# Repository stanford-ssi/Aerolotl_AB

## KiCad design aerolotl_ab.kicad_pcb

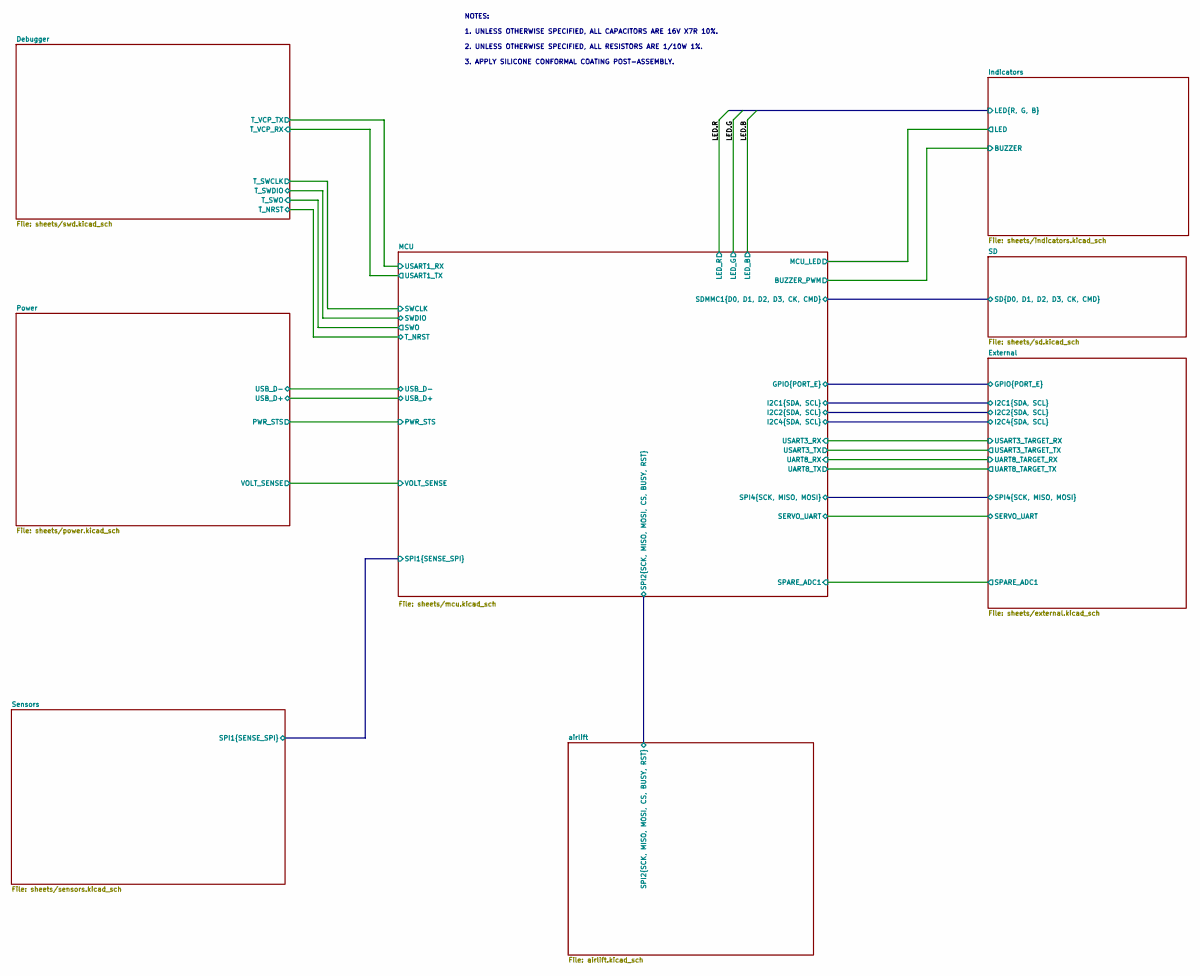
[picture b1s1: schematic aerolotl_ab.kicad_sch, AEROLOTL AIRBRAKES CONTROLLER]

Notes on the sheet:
NOTES: 1. UNLESS OTHERWISE SPECIFIED, ALL CAPACITORS ARE 16V X7R 10%. 2. UNLESS OTHERWISE SPECIFIED, ALL RESISTORS ARE 1/10W 1%. 3. APPLY SILICONE CONFORMAL COATING POST-ASSEMBLY.

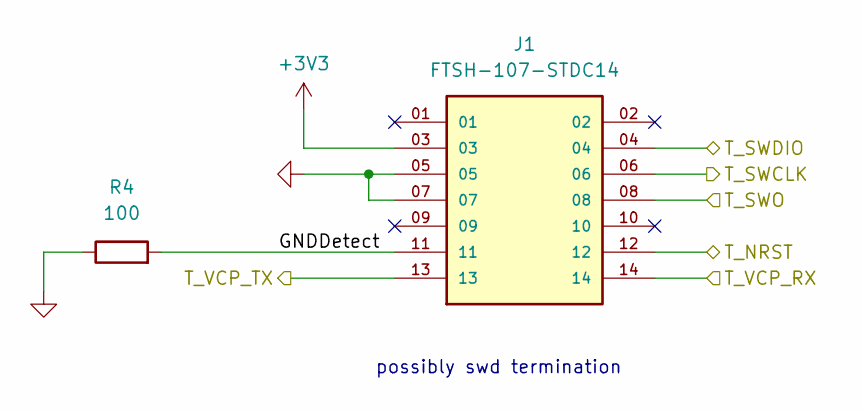
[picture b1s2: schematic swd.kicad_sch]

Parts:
J1: FTSH-107-STDC14; STDC14_SAMTEC_FTSH-107-01-L-DV-K-A; PARTREV H
R4: 100; R_0402_1005Metric

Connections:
+3V3: J1.03; also elsewhere on the board
/Debugger/GNDDetect: J1.11, R4.2
/Debugger/T_NRST: J1.12; also elsewhere on the board
/Debugger/T_SWCLK: J1.06; also elsewhere on the board
/Debugger/T_SWDIO: J1.04; also elsewhere on the board
/Debugger/T_SWO: J1.08; also elsewhere on the board
/Debugger/T_VCP_RX: J1.14; also elsewhere on the board
/Debugger/T_VCP_TX: J1.13; also elsewhere on the board
GND: J1.05, J1.07, R4.1; also elsewhere on the board

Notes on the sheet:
possibly swd termination

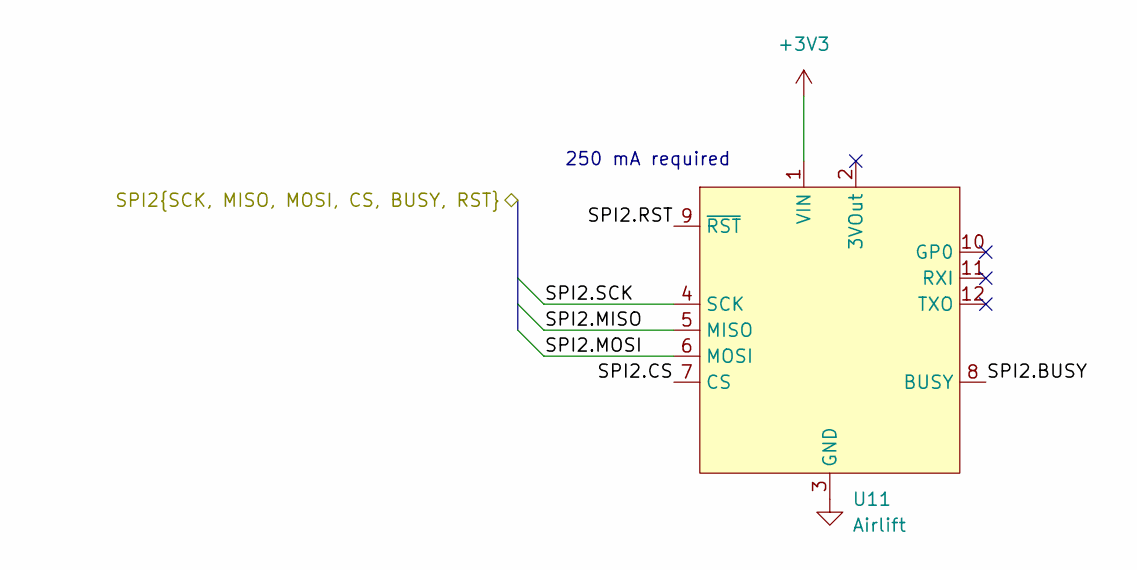
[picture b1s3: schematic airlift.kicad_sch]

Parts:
U11: Airlift; PinSocket_1x12_P2.54mm_Vertical; Mfr. Part No. 4201

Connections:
+3V3: U11.1 (VIN); also elsewhere on the board
/MCU/SPI2.BUSY: U11.8 (BUSY); also elsewhere on the board
/MCU/SPI2.CS: U11.7 (CS); also elsewhere on the board
/MCU/SPI2.MISO: U11.5 (MISO); also elsewhere on the board
/MCU/SPI2.MOSI: U11.6 (MOSI); also elsewhere on the board
/MCU/SPI2.RST: U11.9 (~RST); also elsewhere on the board
/MCU/SPI2.SCK: U11.4 (SCK); also elsewhere on the board
GND: U11.3 (GND); also elsewhere on the board

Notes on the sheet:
250 mA required

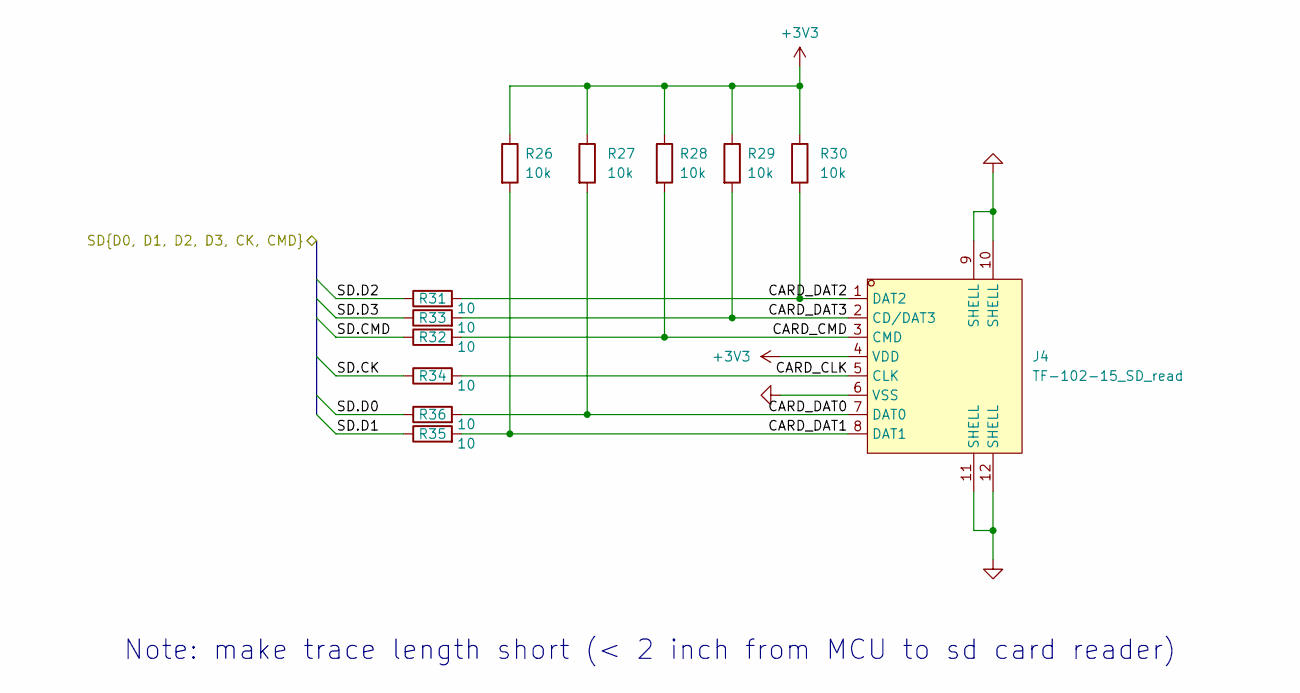
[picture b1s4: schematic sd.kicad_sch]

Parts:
J4: TF-102-15_SD_read; TF-SMD_TF-102-15; LCSC Part C266609
R26, R27, R28, R29, R30: 10k; R_0402_1005Metric; LCSC Part C25744
R31, R32, R33, R34, R35, R36: 10; R_0402_1005Metric

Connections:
+3V3: J4.4 (VDD), R26.1, R27.1, R28.1, R29.1, R30.1; also elsewhere on the board
/MCU/SDMMC1.CK: R34.1; also elsewhere on the board
/MCU/SDMMC1.CMD: R32.1; also elsewhere on the board
/MCU/SDMMC1.D0: R36.1; also elsewhere on the board
/MCU/SDMMC1.D1: R35.1; also elsewhere on the board
/MCU/SDMMC1.D2: R31.1; also elsewhere on the board
/MCU/SDMMC1.D3: R33.1; also elsewhere on the board
/SD/CARD_CLK: J4.5 (CLK), R34.2
/SD/CARD_CMD: J4.3 (CMD), R28.2, R32.2
/SD/CARD_DAT0: J4.7 (DAT0), R27.2, R36.2
/SD/CARD_DAT1: J4.8 (DAT1), R26.2, R35.2
/SD/CARD_DAT2: J4.1 (DAT2), R30.2, R31.2
/SD/CARD_DAT3: J4.2 (CD/DAT3), R29.2, R33.2
GND: J4.6 (VSS), J4.9 (SHELL), J4.10 (SHELL), J4.11 (SHELL), J4.12 (SHELL); also elsewhere on the board

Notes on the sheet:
Note: make trace length short (< 2 inch from MCU to sd card reader)

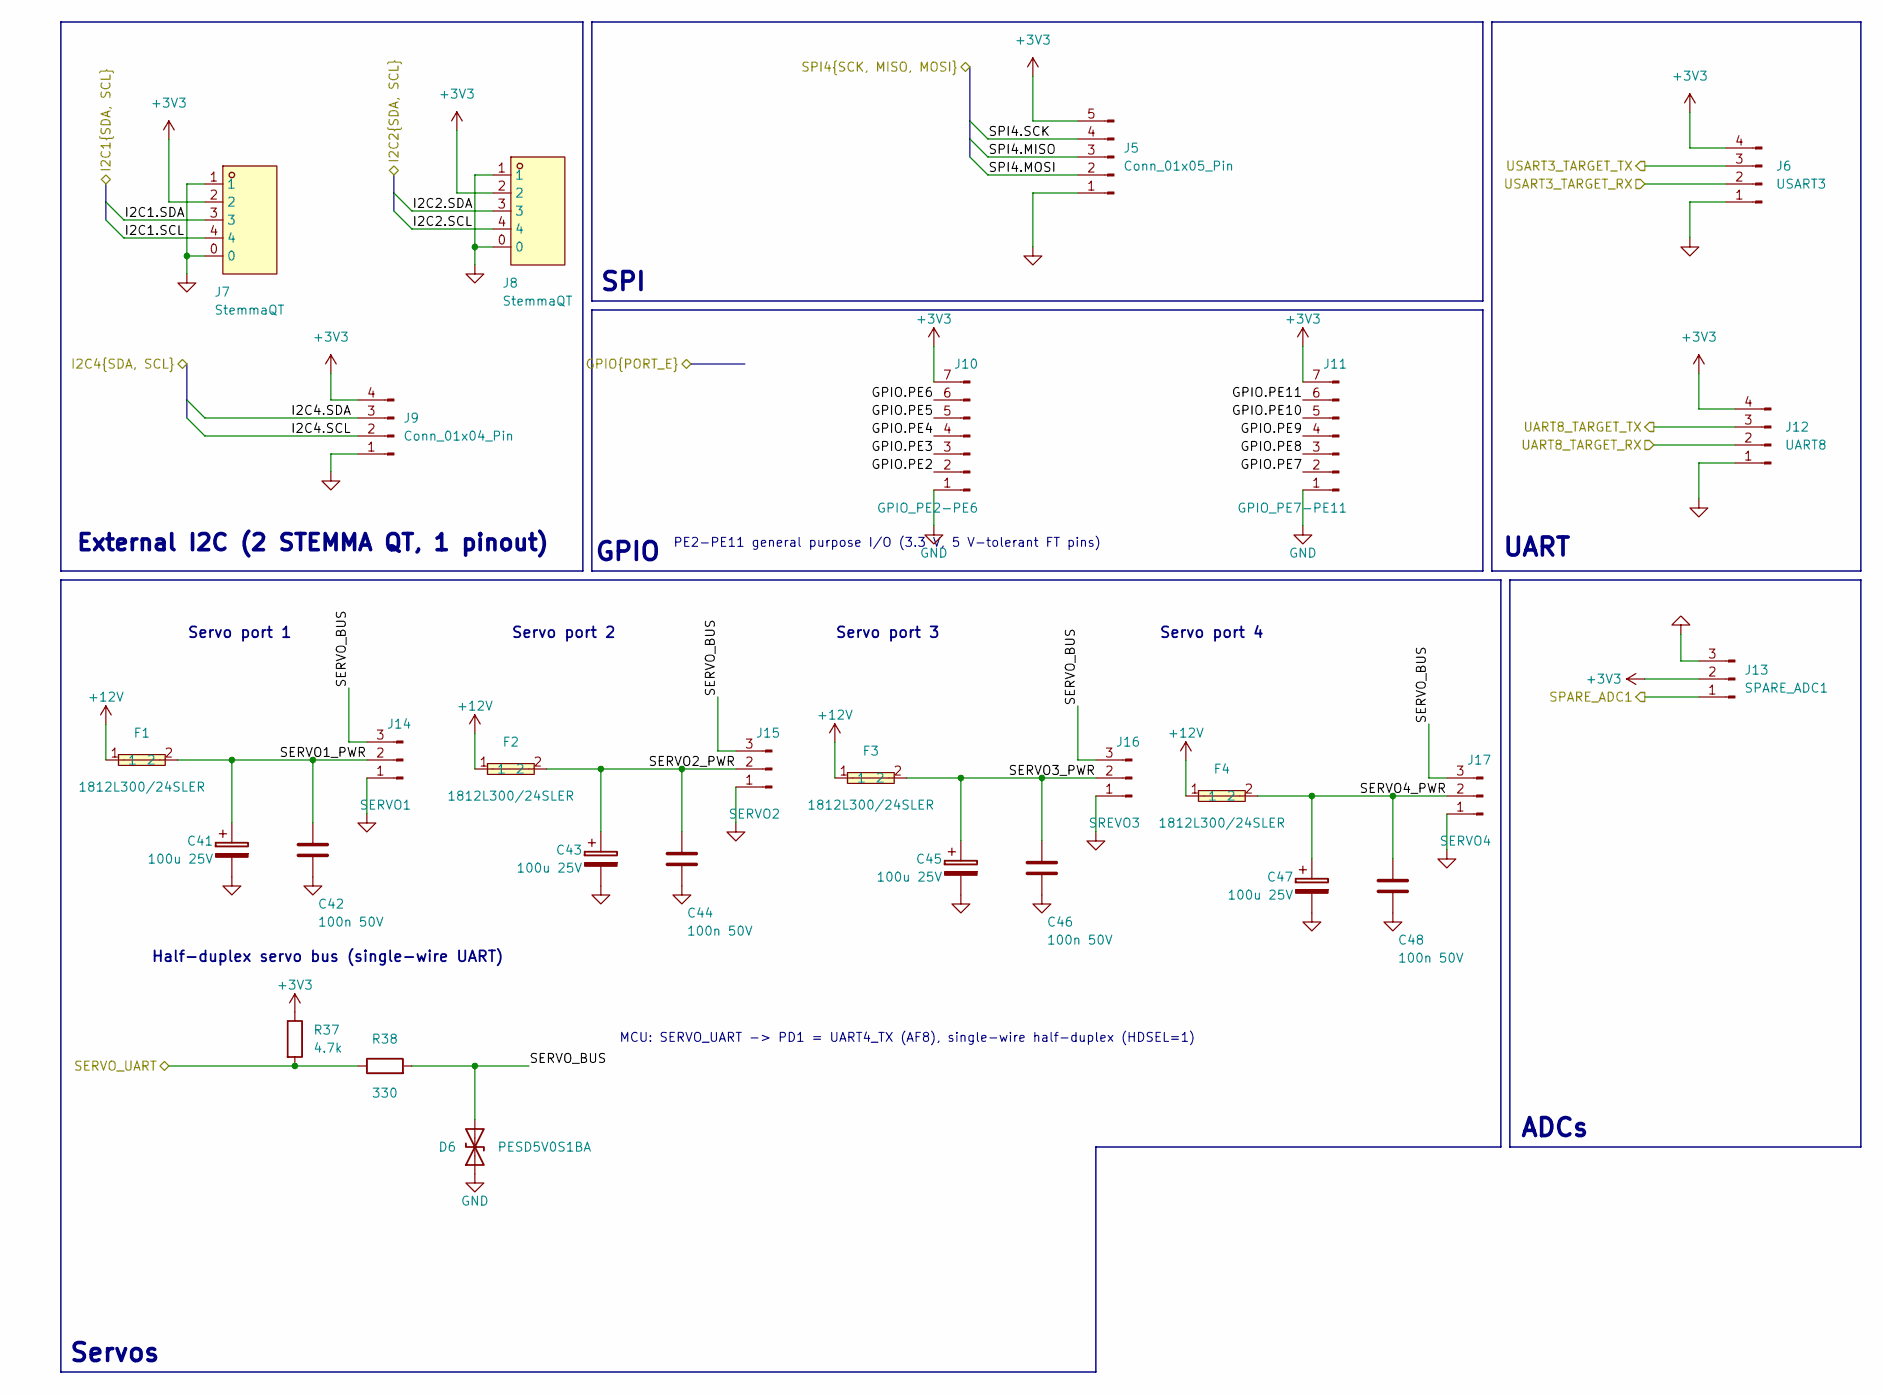
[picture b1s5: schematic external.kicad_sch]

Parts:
C41, C43, C45, C47: 100u 25V; CP_Elec_6.3x7.7
C42, C44, C46, C48: 100n 50V; C_0603_1608Metric
D6: PESD5V0S1BA; D_SOD-323
F1, F2, F3, F4: 1812L300/24SLER; Fuse_1812_4532Metric; LCSC Part C1512049
J5: Conn_01x05_Pin; JST_GH_BM05B-GHS-TBT_1x05-1MP_P1.25mm_Vertical
J6: USART3; JST_GH_BM04B-GHS-TBT_1x04-1MP_P1.25mm_Vertical
J7, J8: StemmaQT; LCSC Part C160390
J9: Conn_01x04_Pin; JST_GH_BM04B-GHS-TBT_1x04-1MP_P1.25mm_Vertical
J10: GPIO_PE2-PE6; JST_GH_BM07B-GHS-TBT_1x07-1MP_P1.25mm_Vertical; MPN SM07B-GHS-TB
J11: GPIO_PE7-PE11; JST_GH_BM07B-GHS-TBT_1x07-1MP_P1.25mm_Vertical; MPN SM07B-GHS-TB
J12: UART8; JST_GH_BM04B-GHS-TBT_1x04-1MP_P1.25mm_Vertical
J13: SPARE_ADC1; JST_GH_BM03B-GHS-TBT_1x03-1MP_P1.25mm_Vertical
J14: SERVO1; Molex_SPOX_5267-03A_1x03_P2.50mm_Vertical; MPN 5267-03A
J15: SERVO2; Molex_SPOX_5267-03A_1x03_P2.50mm_Vertical; MPN 5267-03A
J16: SREVO3; Molex_SPOX_5267-03A_1x03_P2.50mm_Vertical; MPN 5267-03A
J17: SERVO4; Molex_SPOX_5267-03A_1x03_P2.50mm_Vertical; MPN 5267-03A
R37: 4.7k; R_0402_1005Metric
R38: 330; R_0402_1005Metric

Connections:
+3V3: J5.5, J6.4, J7.2, J8.2, J9.4, J10.7, J11.7, J12.4, J13.2, R37.1; also elsewhere on the board
+12V: F1.1, F2.1, F3.1, F4.1; also elsewhere on the board
/External/GPIO.PE2: J10.2; also elsewhere on the board
/External/GPIO.PE3: J10.3; also elsewhere on the board
/External/GPIO.PE4: J10.4; also elsewhere on the board
/External/GPIO.PE5: J10.5; also elsewhere on the board
/External/GPIO.PE6: J10.6; also elsewhere on the board
/External/GPIO.PE7: J11.2; also elsewhere on the board
/External/GPIO.PE8: J11.3; also elsewhere on the board
/External/GPIO.PE9: J11.4; also elsewhere on the board
/External/GPIO.PE10: J11.5; also elsewhere on the board
/External/GPIO.PE11: J11.6; also elsewhere on the board
/External/I2C1.SCL: J7.4; also elsewhere on the board
/External/I2C1.SDA: J7.3; also elsewhere on the board
/External/I2C2.SCL: J8.4; also elsewhere on the board
/External/I2C2.SDA: J8.3; also elsewhere on the board
/External/I2C4.SCL: J9.2; also elsewhere on the board
/External/I2C4.SDA: J9.3; also elsewhere on the board
/External/SERVO1_PWR: C41.1, C42.1, F1.2, J14.2
/External/SERVO2_PWR: C43.1, C44.1, F2.2, J15.2
/External/SERVO3_PWR: C45.1, C46.1, F3.2, J16.2
/External/SERVO4_PWR: C47.1, C48.1, F4.2, J17.2
/External/SERVO_BUS: D6.2 (A2), J14.3, J15.3, J16.3, J17.3, R38.2
/External/SERVO_UART: R37.2, R38.1; also elsewhere on the board
/External/SPARE_ADC1: J13.1; also elsewhere on the board
/External/SPI4.MISO: J5.3; also elsewhere on the board
/External/SPI4.MOSI: J5.2; also elsewhere on the board
/External/SPI4.SCK: J5.4; also elsewhere on the board
/External/UART8_TARGET_RX: J12.2; also elsewhere on the board
/External/UART8_TARGET_TX: J12.3; also elsewhere on the board
/External/USART3_TARGET_RX: J6.2; also elsewhere on the board
/External/USART3_TARGET_TX: J6.3; also elsewhere on the board
GND: C41.2, C42.2, C43.2, C44.2, C45.2, C46.2, C47.2, C48.2, D6.1 (A1), J5.1, J6.1, J7.0, J7.1, J8.0, J8.1, J9.1, J10.1, J11.1, J12.1, J13.3, J14.1, J15.1, J16.1, J17.1; also elsewhere on the board

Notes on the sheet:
Servo port 1
External I2C (2 STEMMA QT, 1 pinout)
SPI
PE2-PE11 general purpose I/O (3.3 V, 5 V-tolerant FT pins)
Servo port 2
GPIO
Half-duplex servo bus (single-wire UART)
Servo port 4
UART
MCU: SERVO_UART -> PD1 = UART4_TX (AF8), single-wire half-duplex (HDSEL=1)
Servo port 3
Servos
ADCs

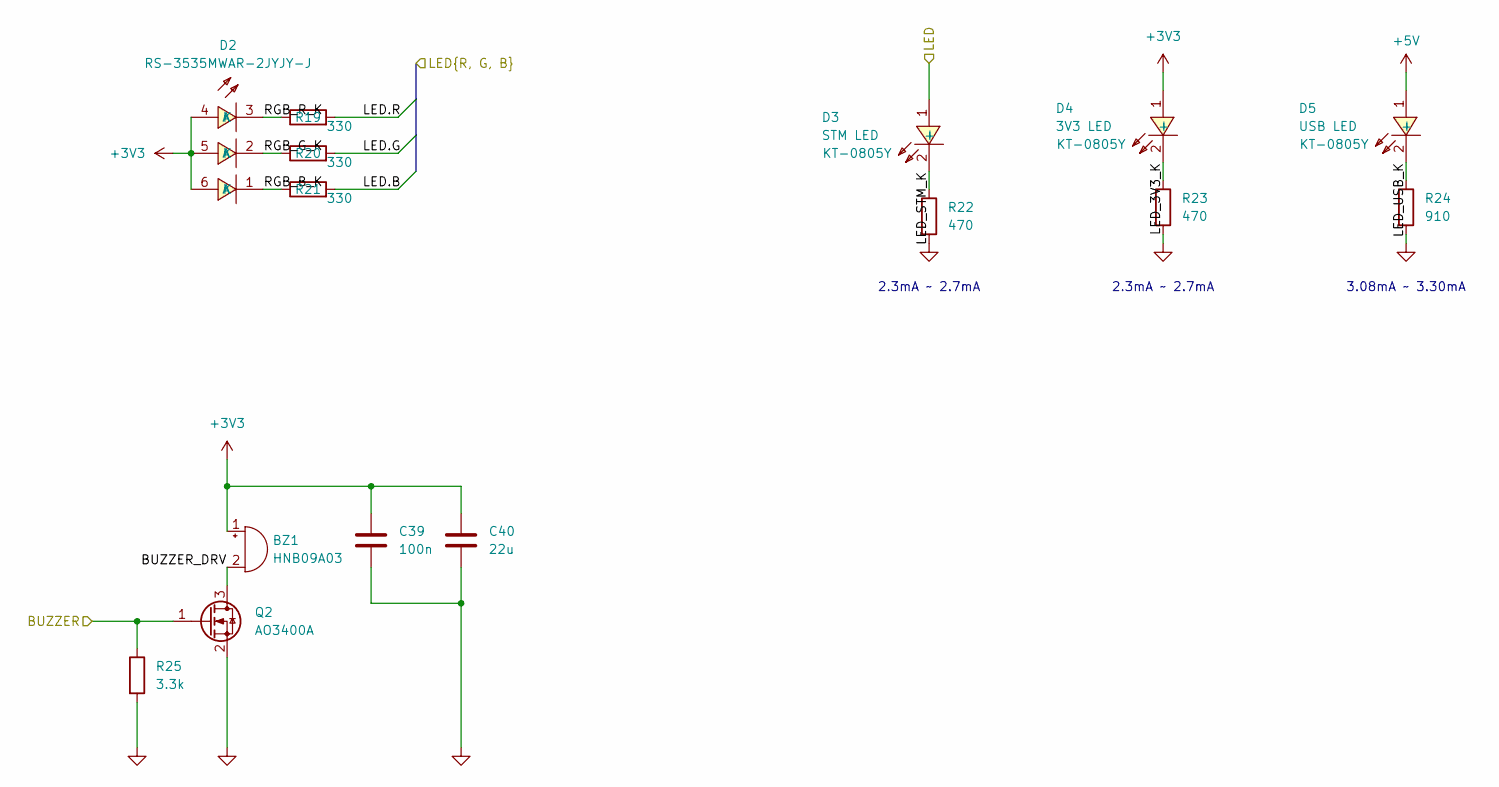
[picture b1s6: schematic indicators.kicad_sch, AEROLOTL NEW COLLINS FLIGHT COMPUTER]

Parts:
BZ1: HNB09A03; BUZ-TH_BD9.0-P5.00-D0.6-FD
C39: 100n; C_0402_1005Metric; LCSC Part C1525
C40: 22u; C_0805_2012Metric; LCSC Part C45783
D2: RS-3535MWAR-2JYJY-J; LED-SMD_RS-3535MWAR-2JYJY-J; MPN RS-3535MWAR; LCSC Part C110402
D3: STM LED; LED0805-R-RD; LCSC Part C2296
D4: 3V3 LED; LED0805-R-RD; LCSC Part C2296
D5: USB LED; LED0805-R-RD; LCSC Part C2296
Q2: AO3400A; SOT-23
R19, R20, R21: 330; R_0402_1005Metric
R22, R23: 470; R_0402_1005Metric
R24: 910; R_0402_1005Metric
R25: 3.3k; R_0402_1005Metric

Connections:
+3V3: BZ1.1 (+), C39.1, C40.1, D2.4 (A), D2.5 (A), D2.6 (A), D4.1 (+); also elsewhere on the board
+5V: D5.1 (+); also elsewhere on the board
/Indicators/BUZZER: Q2.1 (G), R25.1; also elsewhere on the board
/Indicators/BUZZER_DRV: BZ1.2 (-), Q2.3 (D)
/Indicators/LED: D3.1 (+); also elsewhere on the board
/Indicators/LED.B: R21.2; also elsewhere on the board
/Indicators/LED.G: R20.2; also elsewhere on the board
/Indicators/LED.R: R19.2; also elsewhere on the board
/Indicators/LED_3V3_K: D4.2 (-), R23.1
/Indicators/LED_STM_K: D3.2 (-), R22.1
/Indicators/LED_USB_K: D5.2 (-), R24.1
/Indicators/RGB_B_K: D2.1 (K), R21.1
/Indicators/RGB_G_K: D2.2 (K), R20.1
/Indicators/RGB_R_K: D2.3 (K), R19.1
GND: C39.2, C40.2, Q2.2 (S), R22.2, R23.2, R24.2, R25.2; also elsewhere on the board

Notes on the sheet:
2.3mA ~ 2.7mA
3.08mA ~ 3.30mA

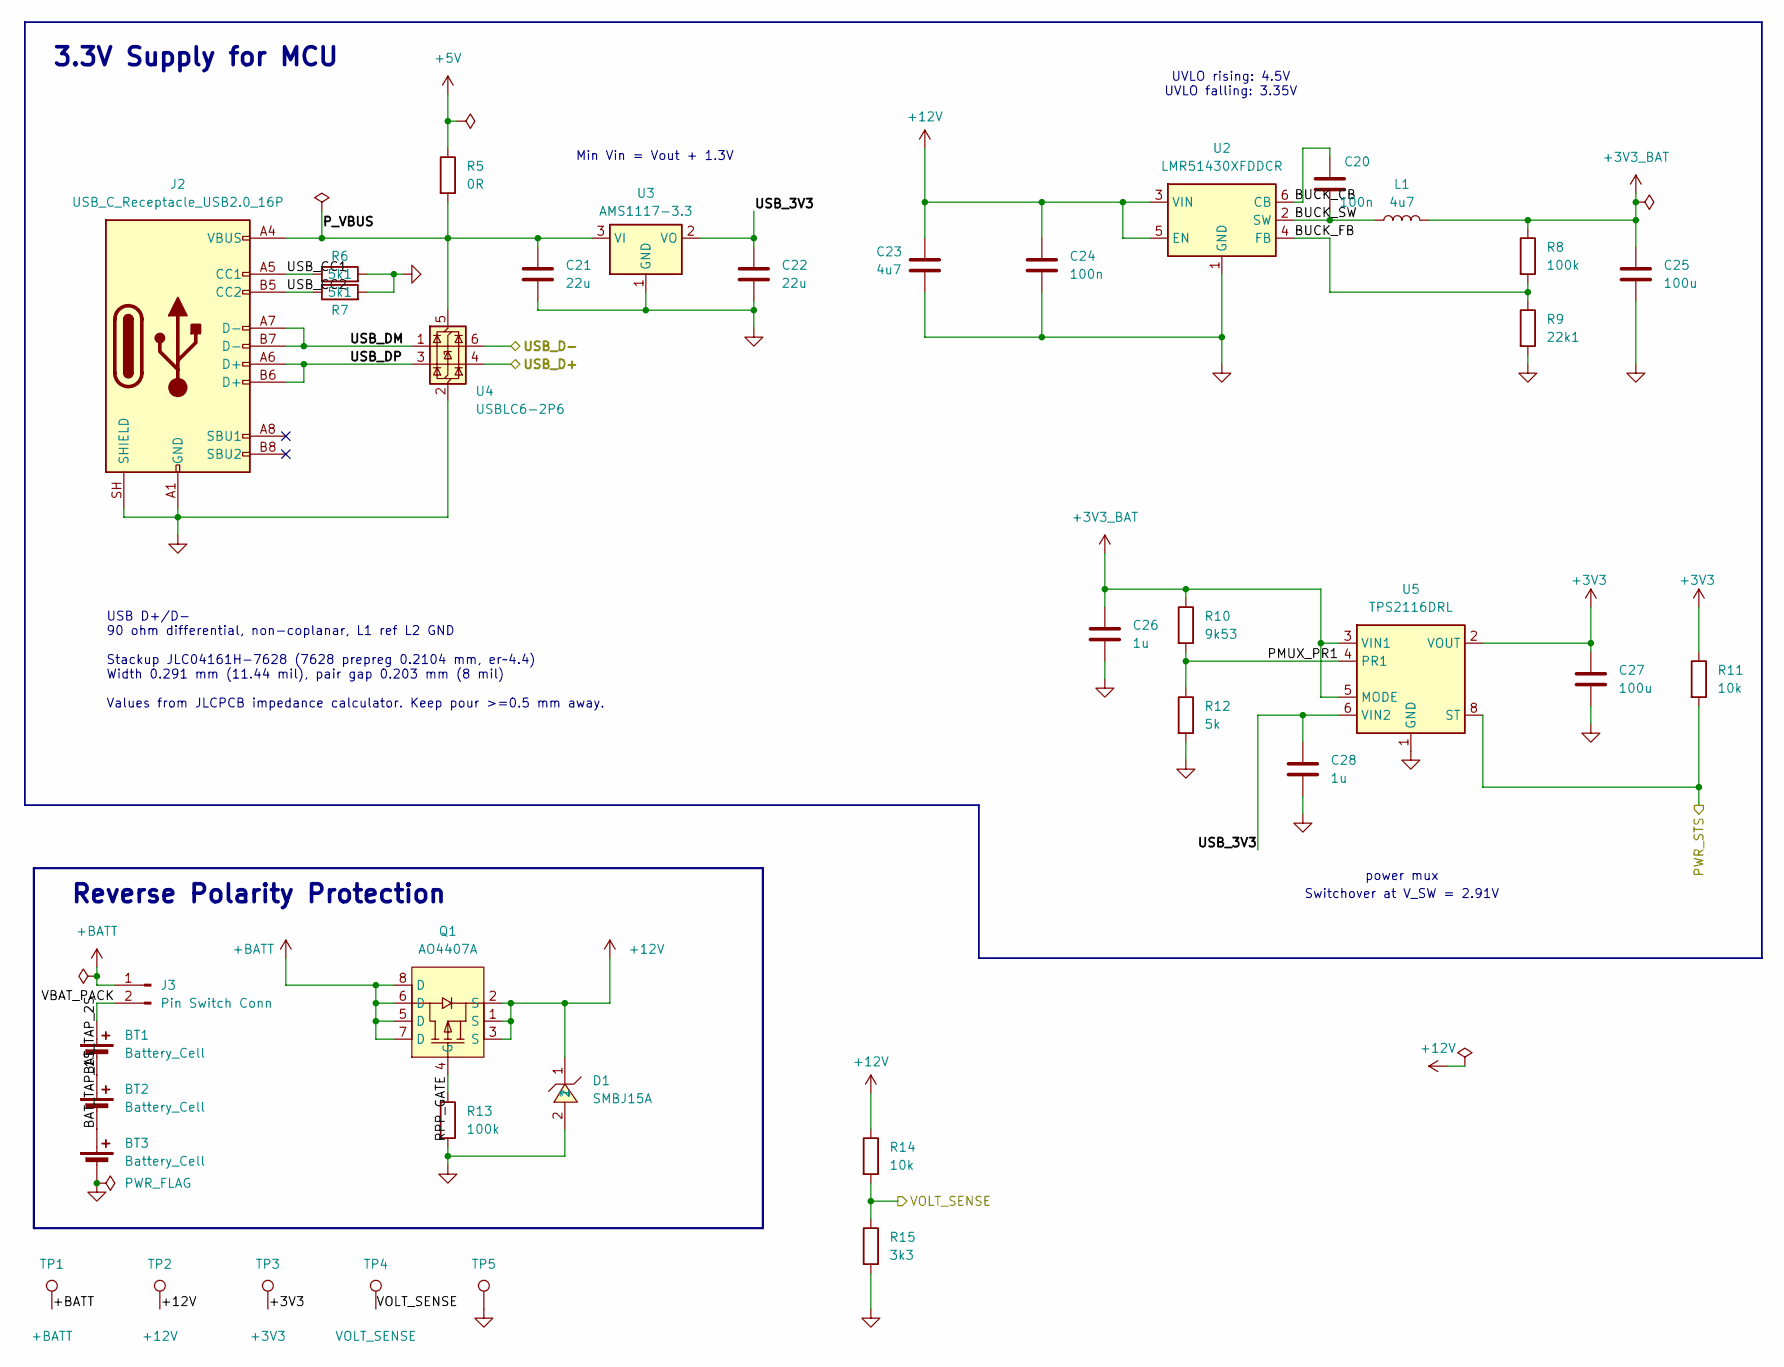
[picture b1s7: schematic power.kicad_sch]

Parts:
BT1, BT2, BT3: Battery_Cell; BatteryHolder_Keystone_1042_1x18650
C20, C24: 100n; C_0603_1608Metric; LCSC Part C14663
C21, C22: 22u; C_0805_2012Metric; LCSC Part C45783
C23: 4u7; C_0805_2012Metric; Voltage 50V
C25, C27: 100u; C_1206_3216Metric
C26, C28: 1u; C_0402_1005Metric
D1: SMBJ15A; SMB_L4.6-W3.6-LS5.3-RD; LCSC Part C83846
J2: USB_C_Receptacle_USB2.0_16P; USB_C_Receptacle_HRO_TYPE-C-31-M-12
J3: Pin Switch Conn; AMASS_XT30PW-M_1x02_P2.50mm_Horizontal
L1: 4u7; L_Sunlord_SWPA4030S
Q1: AO4407A; SOIC-8_L4.9-W3.9-P1.27-LS6.0-BL; LCSC Part C16072
R5: 0R; R_0603_1608Metric
R6, R7: 5k1; R_0402_1005Metric
R8, R13: 100k; R_0402_1005Metric
R9: 22k1; R_0402_1005Metric
R10: 9k53; R_0402_1005Metric
R11, R14: 10k; R_0402_1005Metric; LCSC Part C25744
R12: 5k; R_0402_1005Metric
R15: 3k3; R_0402_1005Metric
TP1: +BATT; TestPoint_Plated_Hole_D2.0mm
TP2: +12V; TestPoint_Plated_Hole_D2.0mm
TP3: +3V3; TestPoint_Plated_Hole_D2.0mm
TP4: VOLT_SENSE; TestPoint_Plated_Hole_D2.0mm
TP5: GND; TestPoint_Plated_Hole_D2.0mm
U2: LMR51430XFDDCR; SOT-23-6
U3: AMS1117-3.3; SOT-223-3_TabPin2
U4: USBLC6-2P6; SOT-666
U5: TPS2116DRL; SOT-583-8; LCSC C3235557

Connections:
+3V3: C27.1, R11.1, TP3.1 (1_1), U5.2 (VOUT), U5.7 (VOUT); also elsewhere on the board
+3V3_BAT: C25.1, C26.1, L1.2, R8.1, R10.1, U5.3 (VIN1), U5.5 (MODE)
+5V: R5.1; also elsewhere on the board
+12V: C23.1, C24.1, D1.1, Q1.1 (S), Q1.2 (S), Q1.3 (S), R14.1, TP2.1 (1_1), U2.3 (VIN), U2.5 (EN); also elsewhere on the board
+BATT: J3.1, Q1.5 (D), Q1.6 (D), Q1.7 (D), Q1.8 (D), TP1.1 (1_1)
/MCU/PWR_STS: R11.2, U5.8 (ST); also elsewhere on the board
/MCU/USB_D+: U4.4 (I/O2); also elsewhere on the board
/MCU/USB_D-: U4.6 (I/O1); also elsewhere on the board
/Power/BAT_TAP_1S: BT2.2 (-), BT3.1 (+)
/Power/BAT_TAP_2S: BT1.2 (-), BT2.1 (+)
/Power/BUCK_CB: C20.1, U2.6 (CB)
/Power/BUCK_FB: R8.2, R9.1, U2.4 (FB)
/Power/BUCK_SW: C20.2, L1.1, U2.2 (SW)
/Power/PMUX_PR1: R10.2, R12.1, U5.4 (PR1)
/Power/P_VBUS: C21.1, J2.A4 (VBUS), J2.A9 (VBUS), J2.B4 (VBUS), J2.B9 (VBUS), R5.2, U3.3 (VI), U4.5 (VBUS)
/Power/RPP_GATE: Q1.4 (G), R13.1
/Power/USB_3V3: C22.1, C28.1, U3.2 (VO), U5.6 (VIN2)
/Power/USB_CC1: J2.A5 (CC1), R6.1
/Power/USB_CC2: J2.B5 (CC2), R7.1
/Power/USB_DM: J2.A7 (D-), J2.B7 (D-), U4.1 (I/O1)
/Power/USB_DP: J2.A6 (D+), J2.B6 (D+), U4.3 (I/O2)
/Power/VBAT_PACK: BT1.1 (+), J3.2
/Power/VOLT_SENSE: R14.2, R15.1, TP4.1 (1_1); also elsewhere on the board
GND: BT3.2 (-), C21.2, C22.2, C23.2, C24.2, C25.2, C26.2, C27.2, C28.2, D1.2, J2.A1 (GND), J2.A12 (GND), J2.B1 (GND), J2.B12 (GND), J2.SH (SHIELD), R6.2, R7.2, R9.2, R12.2, R13.2, R15.2, TP5.1 (1_1), U2.1 (GND), U3.1 (GND), U4.2 (GND), U5.1 (GND); also elsewhere on the board

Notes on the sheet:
3.3V Supply for MCU
power mux
Switchover at V_SW = 2.91V
Reverse Polarity Protection
UVLO rising: 4.5V UVLO falling: 3.35V
Min Vin = Vout + 1.3V
USB D+/D- 90 ohm differential, non-coplanar, L1 ref L2 GND Stackup JLC04161H-7628 (7628 prepreg 0.2104 mm, er~4.4) Width 0.291 mm (11.44 mil), pair gap 0.203 mm (8 mil) Values from JLCPCB impedance calculator. Keep pour >=0.5 mm away.

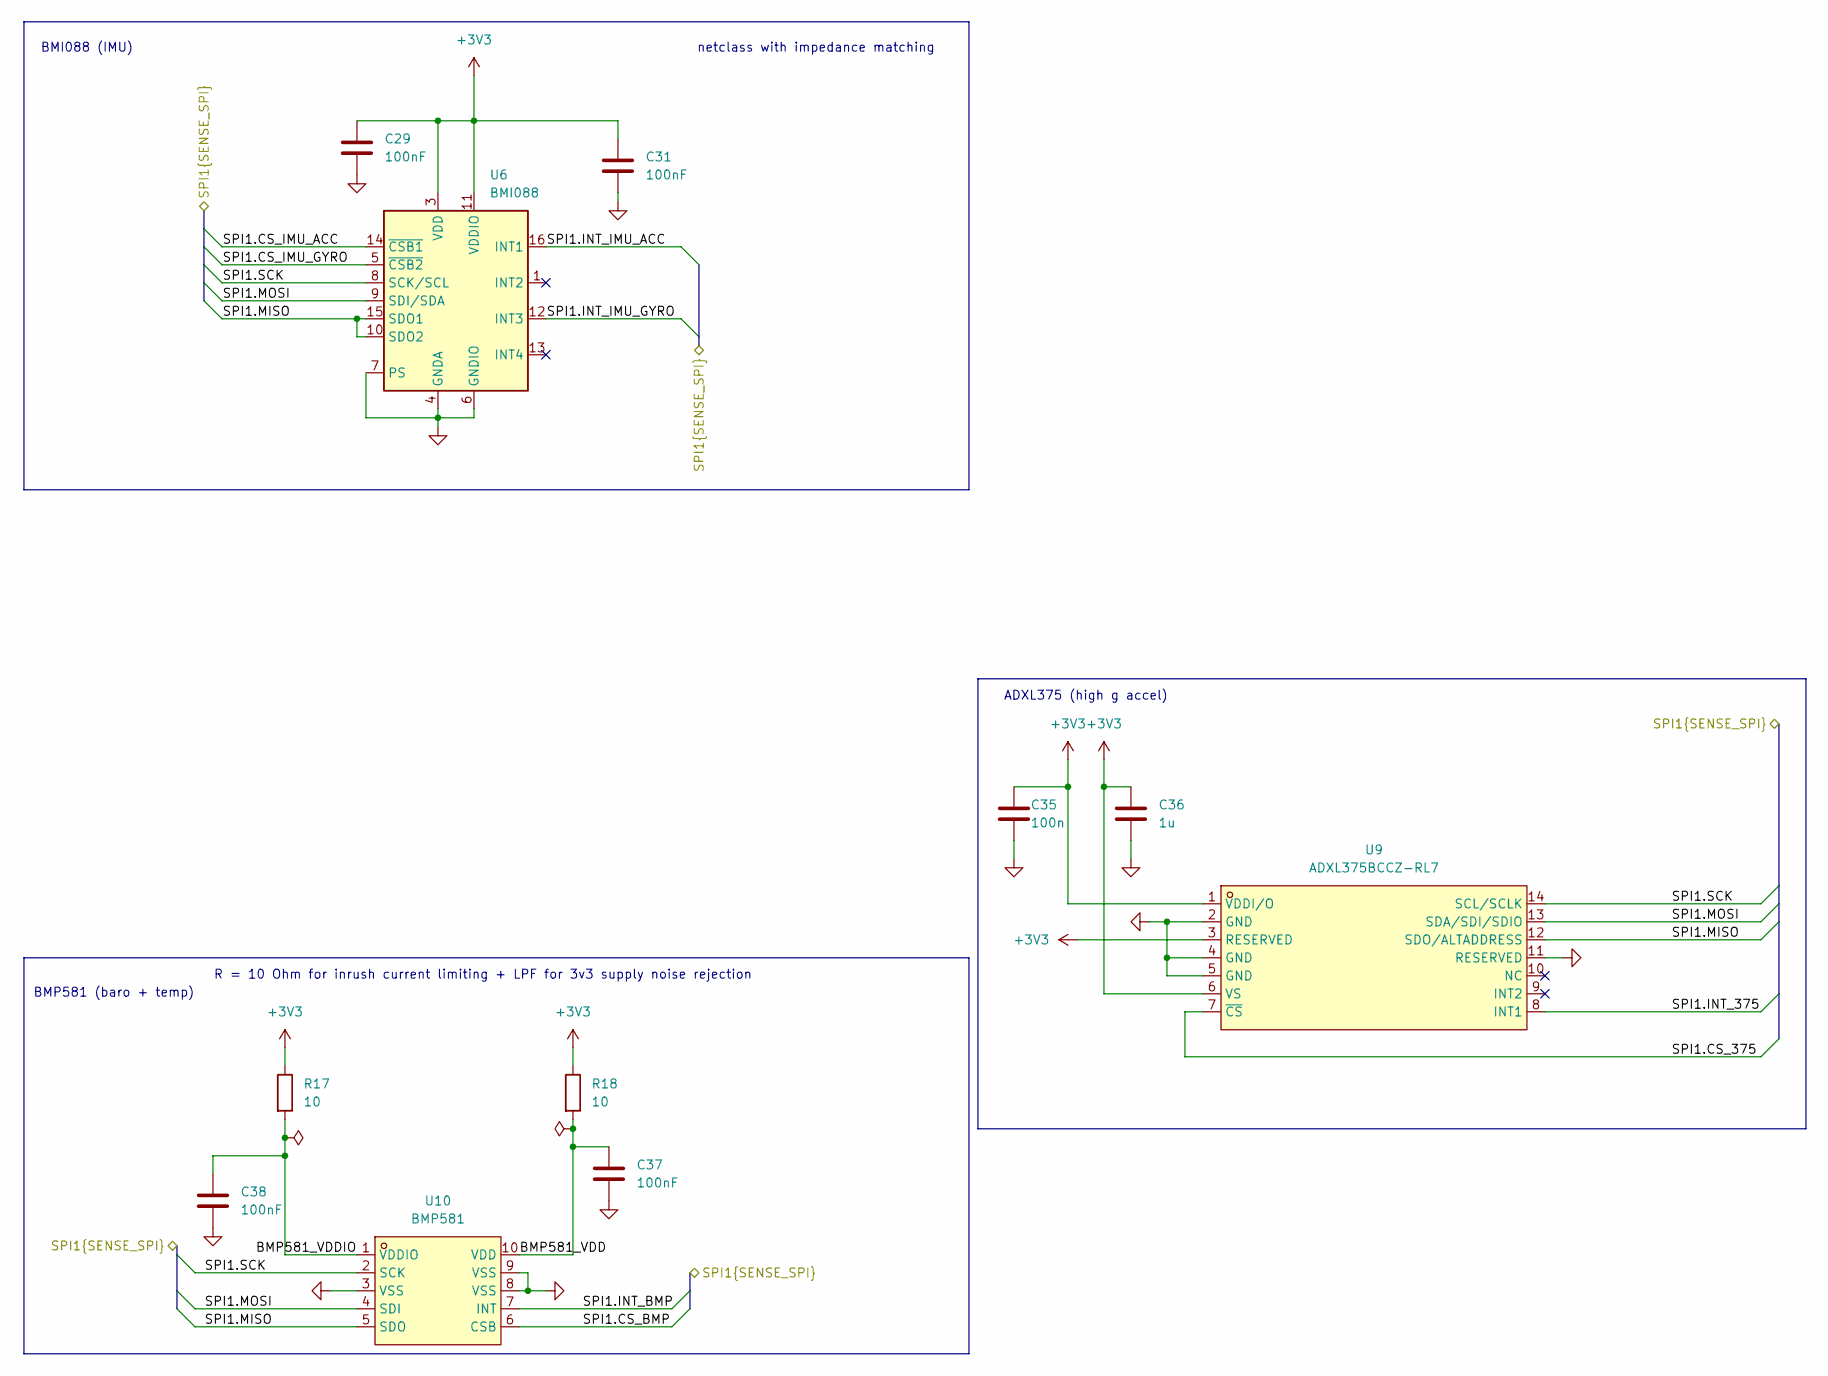
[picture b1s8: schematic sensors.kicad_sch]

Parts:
C29, C31, C37, C38: 100nF; C_0402_1005Metric; LCSC Part C1525
C35: 100n; C_0402_1005Metric; LCSC Part C1525
C36: 1u; C_0402_1005Metric
R17, R18: 10; R_0402_1005Metric
U6: BMI088; Bosch_LGA-16_4.5x3mm_P0.5mm_LayoutBorder7x1y_ClockwisePinNu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
U9: ADXL375BCCZ-RL7; ADXL375_LGA-14_L5.0-W3.0-P0.80-BL; LCSC Part C481898
U10: BMP581; LGA-10_L2.0-W2.0-P0.50-TL_BMP581; LCSC Part C5362283

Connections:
+3V3: C29.1, C31.1, C35.1, C36.1, R17.1, R18.1, U6.3 (VDD), U6.11 (VDDIO), U9.1 (VDDI/O), U9.3 (RESERVED), U9.6 (VS); also elsewhere on the board
/MCU/SPI1.CS_375: U9.7 (~CS); also elsewhere on the board
/MCU/SPI1.CS_BMP: U10.6 (CSB); also elsewhere on the board
/MCU/SPI1.CS_IMU_ACC: U6.14 (~CSB1); also elsewhere on the board
/MCU/SPI1.CS_IMU_GYRO: U6.5 (~CSB2); also elsewhere on the board
/MCU/SPI1.INT_375: U9.8 (INT1); also elsewhere on the board
/MCU/SPI1.INT_BMP: U10.7 (INT); also elsewhere on the board
/MCU/SPI1.INT_IMU_ACC: U6.16 (INT1); also elsewhere on the board
/MCU/SPI1.INT_IMU_GYRO: U6.12 (INT3); also elsewhere on the board
/MCU/SPI1.MISO: U6.10 (SDO2), U6.15 (SDO1), U9.12 (SDO/ALTADDRESS), U10.5 (SDO); also elsewhere on the board
/MCU/SPI1.MOSI: U6.9 (SDI/SDA), U9.13 (SDA/SDI/SDIO), U10.4 (SDI); also elsewhere on the board
/MCU/SPI1.SCK: U6.8 (SCK/SCL), U9.14 (SCL/SCLK), U10.2 (SCK); also elsewhere on the board
/Sensors/BMP581_VDD: C37.1, R18.2, U10.10 (VDD)
/Sensors/BMP581_VDDIO: C38.1, R17.2, U10.1 (VDDIO)
GND: C29.2, C31.2, C35.2, C36.2, C37.2, C38.2, U6.2 (GNDA), U6.4 (GNDA), U6.6 (GNDIO), U6.7 (PS), U9.2 (GND), U9.4 (GND), U9.5 (GND), U9.11 (RESERVED), U10.3 (VSS), U10.8 (VSS), U10.9 (VSS); also elsewhere on the board

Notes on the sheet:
ADXL375 (high g accel)
R = 10 Ohm for inrush current limiting + LPF for 3v3 supply noise rejection
BMI088 (IMU)
netclass with impedance matching
BMP581 (baro + temp)

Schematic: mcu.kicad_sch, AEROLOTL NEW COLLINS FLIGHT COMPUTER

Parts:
C1: 100n; C_0603_1608Metric
C2: 4.7u; C_0805_2012Metric; Tolerance 10%; Voltage 16V
C3, C4, C5, C6, C7, C8, C9, C12: 100n; C_0402_1005Metric
C10, C11, C13: 1u; C_0603_1608Metric
C14, C15, C18, C19: 15p; C_0402_1005Metric
C16, C17: 2u2; C_0402_1005Metric
FB1: 100; L_0805_2012Metric
H1, H2: MountingHole; MountingHole_6.4mm_M6_ISO7380
R1, R2: 10k; R_0603_1608Metric
R3: 47; R_0402_1005Metric
SW1: SW_SPST; SW_SPST_TL3342
SW2: SW_Push; SW_SPST_TL3342
U1: STM32H723VGTx; LQFP-100_14x14mm_P0.5mm
Y1: X322525MOB4SI; CRYSTAL-SMD_4P-L3.2-W2.5-BL; LCSC Part C9006
Y2: 32k768; Crystal_SMD_3215-2Pin_3.2x1.5mm; mfr. part no. Q13FC13500004

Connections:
+3.3VA: C9.1, C10.1, FB1.1, R3.1, U1.21 (VDDA)
+3V3: C2.1, C3.1, C4.1, C5.1, C6.1, C7.1, C8.1, C11.1, FB1.2, R1.1, SW1.2 (B), U1.6 (VBAT), U1.11 (VDD), U1.27 (VDD), U1.50 (VDD), U1.75 (VDD), U1.100 (VDD); also elsewhere on the board
/Debugger/T_NRST: C1.1, R1.2, SW2.2, U1.14 (NRST); also elsewhere on the board
/Debugger/T_SWCLK: U1.76 (DEBUG_JTCK-SWCLK); also elsewhere on the board
/Debugger/T_SWDIO: U1.72 (DEBUG_JTMS-SWDIO); also elsewhere on the board
/Debugger/T_SWO: U1.89 (DEBUG_JTDO-SWO); also elsewhere on the board
/Debugger/T_VCP_RX: U1.68 (USART1_TX); also elsewhere on the board
/Debugger/T_VCP_TX: U1.69 (USART1_RX); also elsewhere on the board
/External/GPIO.PE2: U1.1 (PE2); also elsewhere on the board
/External/GPIO.PE3: U1.2 (PE3); also elsewhere on the board
/External/GPIO.PE4: U1.3 (PE4); also elsewhere on the board
/External/GPIO.PE5: U1.4 (PE5); also elsewhere on the board
/External/GPIO.PE6: U1.5 (PE6); also elsewhere on the board
/External/GPIO.PE7: U1.37 (PE7); also elsewhere on the board
/External/GPIO.PE8: U1.38 (PE8); also elsewhere on the board
/External/GPIO.PE9: U1.39 (PE9); also elsewhere on the board
/External/GPIO.PE10: U1.40 (PE10); also elsewhere on the board
/External/GPIO.PE11: U1.41 (PE11); also elsewhere on the board
/External/I2C1.SCL: U1.92 (I2C1_SCL); also elsewhere on the board
/External/I2C1.SDA: U1.93 (I2C1_SDA); also elsewhere on the board
/External/I2C2.SCL: U1.46 (I2C2_SCL); also elsewhere on the board
/External/I2C2.SDA: U1.47 (I2C2_SDA); also elsewhere on the board
/External/I2C4.SCL: U1.59 (PD12); also elsewhere on the board
/External/I2C4.SDA: U1.60 (PD13); also elsewhere on the board
/External/SERVO_UART: U1.82 (UART4_TX); also elsewhere on the board
/External/SPARE_ADC1: U1.28 (PA4); also elsewhere on the board
/External/SPI4.MISO: U1.43 (SPI4_MISO); also elsewhere on the board
/External/SPI4.MOSI: U1.44 (SPI4_MOSI); also elsewhere on the board
/External/SPI4.SCK: U1.42 (SPI4_SCK); also elsewhere on the board
/External/UART8_TARGET_RX: U1.97 (UART8_RX); also elsewhere on the board
/External/UART8_TARGET_TX: U1.98 (UART8_TX); also elsewhere on the board
/External/USART3_TARGET_RX: U1.56 (USART3_RX); also elsewhere on the board
/External/USART3_TARGET_TX: U1.55 (USART3_TX); also elsewhere on the board
/Indicators/BUZZER: U1.67 (TIM1_CH1); also elsewhere on the board
/Indicators/LED: U1.77 (PA15(JTDI)); also elsewhere on the board
/Indicators/LED.B: U1.63 (PC6); also elsewhere on the board
/Indicators/LED.G: U1.33 (PC5); also elsewhere on the board
/Indicators/LED.R: U1.32 (PC4); also elsewhere on the board
/MCU/BOOT0: R2.1, SW1.1 (A), U1.94 (BOOT0)
/MCU/HS_OSC_A: C14.1, U1.12 (RCC_OSC_IN), Y1.1 (OSC1)
/MCU/HS_OSC_B: C15.1, U1.13 (RCC_OSC_OUT), Y1.3 (OSC2)
/MCU/LS_OSC_A: C19.1, U1.8 (RCC_OSC32_IN), Y2.2
/MCU/LS_OSC_B: C18.1, U1.9 (RCC_OSC32_OUT), Y2.1
/MCU/PWR_STS: U1.16 (PC1); also elsewhere on the board
/MCU/SDMMC1.CK: U1.80 (SDMMC1_CK); also elsewhere on the board
/MCU/SDMMC1.CMD: U1.83 (SDMMC1_CMD); also elsewhere on the board
/MCU/SDMMC1.D0: U1.65 (SDMMC1_D0); also elsewhere on the board
/MCU/SDMMC1.D1: U1.66 (SDMMC1_D1); also elsewhere on the board
/MCU/SDMMC1.D2: U1.78 (SDMMC1_D2); also elsewhere on the board
/MCU/SDMMC1.D3: U1.79 (SDMMC1_D3); also elsewhere on the board
/MCU/SPI1.CS_375: U1.88 (PD7); also elsewhere on the board
/MCU/SPI1.CS_BMP: U1.86 (PD5); also elsewhere on the board
/MCU/SPI1.CS_IMU_ACC: U1.84 (PD3); also elsewhere on the board
/MCU/SPI1.CS_IMU_GYRO: U1.85 (PD4); also elsewhere on the board
/MCU/SPI1.INT_375: U1.95 (PB8); also elsewhere on the board
/MCU/SPI1.INT_BMP: U1.96 (PB9); also elsewhere on the board
/MCU/SPI1.INT_IMU_ACC: U1.45 (PE15); also elsewhere on the board
/MCU/SPI1.INT_IMU_GYRO: U1.36 (PB2); also elsewhere on the board
/MCU/SPI1.MISO: U1.30 (SPI1_MISO); also elsewhere on the board
/MCU/SPI1.MOSI: U1.31 (SPI1_MOSI); also elsewhere on the board
/MCU/SPI1.SCK: U1.29 (SPI1_SCK); also elsewhere on the board
/MCU/SPI2.BUSY: U1.57 (PD10); also elsewhere on the board
/MCU/SPI2.CS: U1.51 (PB12); also elsewhere on the board
/MCU/SPI2.MISO: U1.53 (SPI2_MISO); also elsewhere on the board
/MCU/SPI2.MOSI: U1.54 (SPI2_MOSI); also elsewhere on the board
/MCU/SPI2.RST: U1.58 (PD11); also elsewhere on the board
/MCU/SPI2.SCK: U1.52 (SPI2_SCK); also elsewhere on the board
/MCU/USB_D+: U1.71 (USB_OTG_HS_DP); also elsewhere on the board
/MCU/USB_D-: U1.70 (USB_OTG_HS_DM); also elsewhere on the board
/MCU/VCAP1: C16.1, U1.48 (VCAP)
/MCU/VCAP2: C17.1, U1.73 (VCAP)
/MCU/VREFP: C12.1, C13.1, R3.2, U1.20 (VREF+)
/Power/VOLT_SENSE: U1.15 (PC0); also elsewhere on the board
GND: C1.2, C2.2, C3.2, C4.2, C5.2, C6.2, C7.2, C8.2, C9.2, C10.2, C11.2, C12.2, C13.2, C14.2, C15.2, C16.2, C17.2, C18.2, C19.2, R2.2, SW2.1, U1.10 (VSS), U1.19 (VSSA), U1.26 (VSS), U1.49 (VSS), U1.74 (VSS), U1.99 (VSS), Y1.2 (GND), Y1.4 (GND); also elsewhere on the board

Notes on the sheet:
Used in VCP for SWD
MCU Power Management
Place R2 and C24 close to NRST pin
VREF+ and VDDA cap layout from Fig. 38
Check RM0468 p2118/3357 USART_CR3 HDSEL register for half duplex uart needed on ozrobotics motor
Add NRST silkscreen on SW1
MCU Pinouts
